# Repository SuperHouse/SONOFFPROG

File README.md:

Sonoff Programming Adapter
==========================
Copyright 2018 SuperHouse Pty Ltd  www.superhouse.tv  
Designed by Jonathan Oxer

Converts a standard FTDI-type USB-to-Serial adapter into a format
to match the programming header on a Sonoff.

 - Connects directly to FTDI cable
 - Switch to allow target device to be power cycled for flashing

More information available at www.superhouse.tv/sonoffprog

INSTALLATION
------------
The design is saved as an EAGLE project. EAGLE PCB design software is
available from www.cadsoftusa.com free for non-commercial use. To use
this project download it and place the directory containing these files
into the "eagle" directory on your computer. Then open EAGLE and
navigate to the project.

DISTRIBUTION
------------
The specific terms of distribution of this project are governed by the
license referenced below.

LICENSE
-------
Licensed under the TAPR Open Hardware License (www.tapr.org/OHL).
The "license" folder within this repository also contains a copy of
this license in plain text format.

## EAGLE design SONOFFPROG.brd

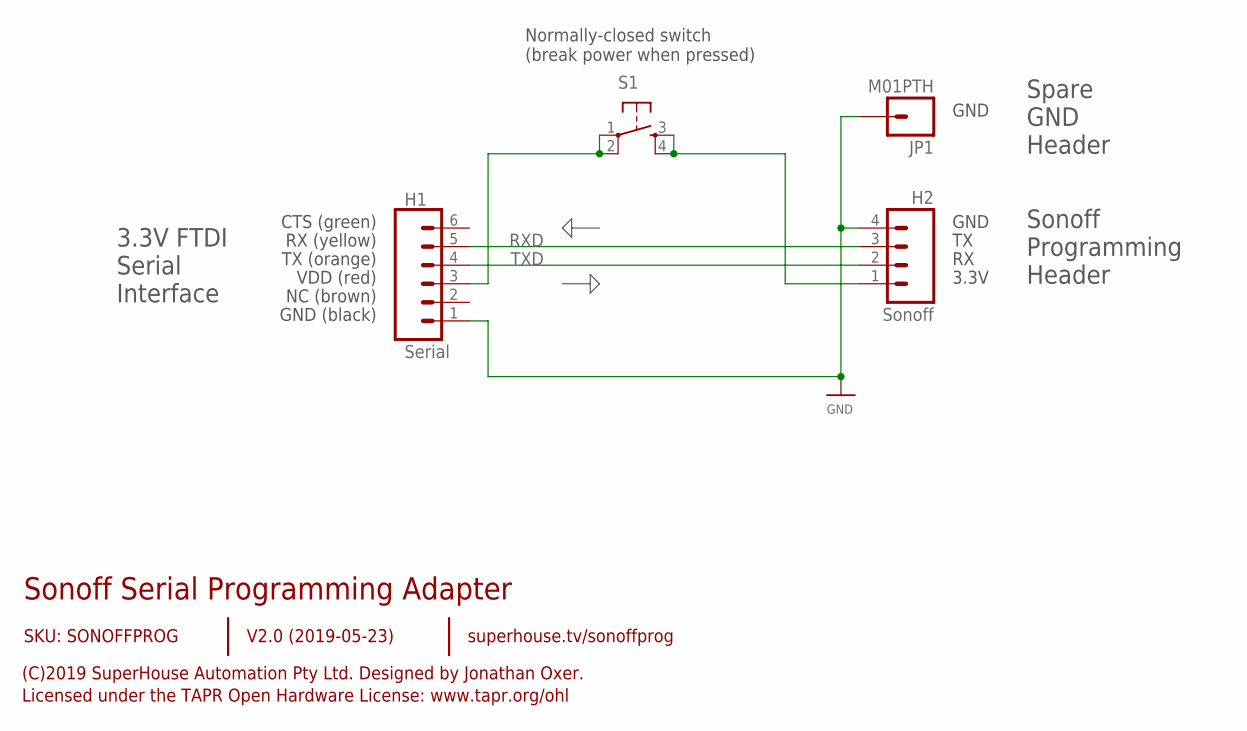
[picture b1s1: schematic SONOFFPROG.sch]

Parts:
H1: Serial; 1X06
H2: Sonoff; 1X04
JP1: M01PTH; 1X01
S1: TAC_SWITCHPTH; TACTILE-PTH

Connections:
GND: H1.1, H2.4, JP1.1
unnamed: H2.1, S1.3, S1.4
unnamed: H1.3, S1.1, S1.2
RXD: H1.5, H2.3
TXD: H1.4, H2.2

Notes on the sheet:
Sonoff Serial Programming Adapter
V2.0 (2019-05-23)
SKU: SONOFFPROG
(C)2019 SuperHouse Automation Pty Ltd. Designed by Jonathan Oxer.
Licensed under the TAPR Open Hardware License: www.tapr.org/ohl
superhouse.tv/sonoffprog
CTS (green)
RX (yellow)
TX (orange)
VDD (red)
NC (brown)
GND (black)
3.3V
GND
3.3V FTDI Serial Interface
Sonoff Programming Header
Spare GND Header
Normally-closed switch (break power when pressed)

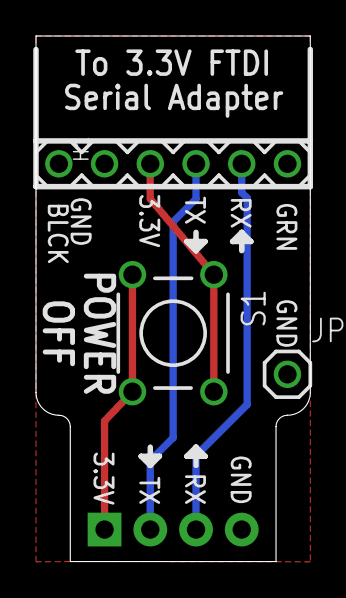
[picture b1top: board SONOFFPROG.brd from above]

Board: 2 copper layers, 15.2 x 29.2 mm, 4 parts (1 on the bottom side), 5 nets.

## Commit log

2018-02-16 Initial project import
2018-03-09 Fixed silkscreen for v1.0 release
2018-07-22 Added URL
2018-07-27 Fixed URLs
2019-06-10 Replaced jumper with NC button, and added GND header for v2.0 release

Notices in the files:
parts and their libraries:
freetronics-original: Licensing: CC v3.0 Share-Alike You are welcome to use this library for commercial purposes.
